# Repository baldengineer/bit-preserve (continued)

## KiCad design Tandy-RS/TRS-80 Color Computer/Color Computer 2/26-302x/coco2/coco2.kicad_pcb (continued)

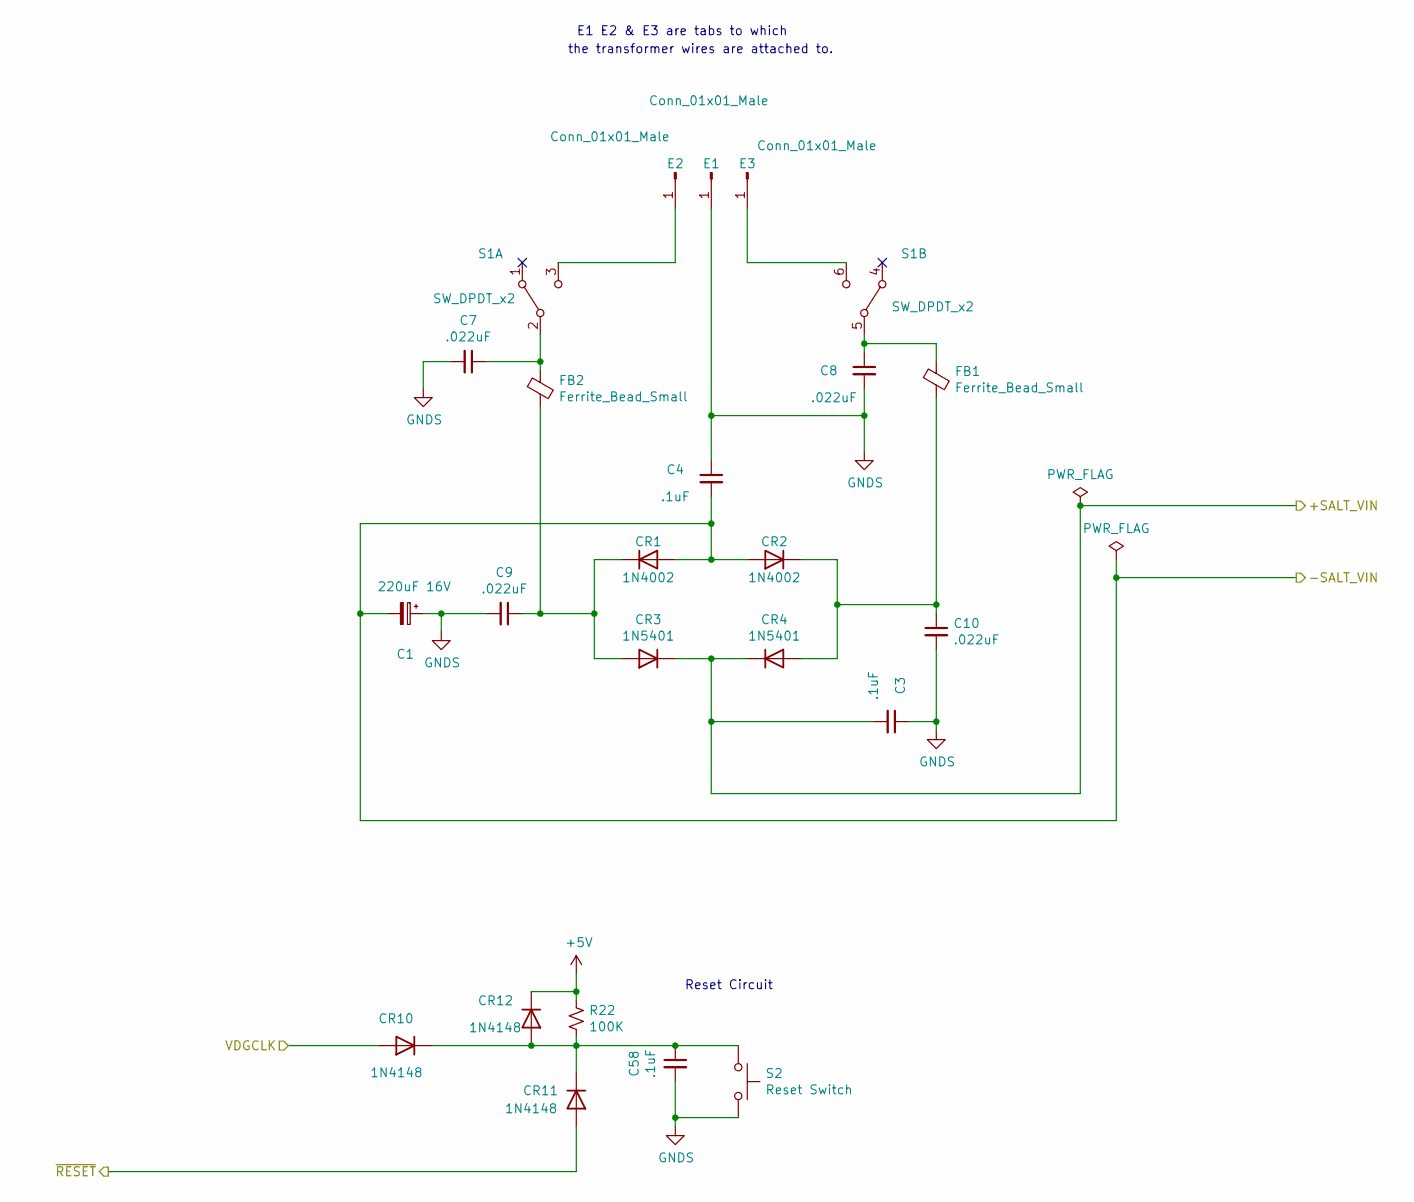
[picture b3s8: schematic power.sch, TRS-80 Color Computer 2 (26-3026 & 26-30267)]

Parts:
C1: 220uF 16V; CP_Radial_D8.0mm_P5.00mm; Manufacturer part# URS1C221MPD1TA
C3, C4, C58: .1uF; C_Axial_L3.8mm_D2.6mm_P10.00mm_Horizontal; Manufacturer part# A104K15X7RF5TAA
C7, C8, C9, C10: .022uF; C_Disc_D8.0mm_W2.5mm_P5.00mm; Manufacturer part# C317C223M5U5TA7301
CR1, CR2: 1N4002; D_DO-41_SOD81_P10.16mm_Horizontal; Manufacturer part# 1N4002G
CR3, CR4: 1N5401; D_DO-201AD_P15.24mm_Horizontal; Manufacturer part# 1N5401G-T
CR10, CR11, CR12: 1N4148; D_DO-35_SOD27_P7.62mm_Horizontal; Manufacturer part# 1N4148
E1, E2, E3: Conn_01x01_Male; Pin_D1.4mm_L8.5mm_W2.8mm_FlatFork; Manufacturer part# 1211
FB1, FB2: Ferrite_Bead_Small; ferrite_bead; Manufacturer part# 2743007111
R22: 100K; R_Axial_DIN0207_L6.3mm_D2.5mm_P10.16mm_Horizontal; Manufacturer part# CF14JT100K
S1: SW_DPDT_x2; F2UEE; Manufacturer part# F2UEE
S2: Reset Switch; B3F3152; Manufacturer part# B3F-3152

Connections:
+5V: CR12.1 (K), R22.1; also elsewhere on the board
/peripherals/+SALT_VIN: C3.2, CR3.1 (K), CR4.1 (K); also elsewhere on the board
/peripherals/-SALT_VIN: C1.2, C4.2, CR1.2 (A), CR2.2 (A); also elsewhere on the board
/power/VDGCLK: CR10.2 (A); also elsewhere on the board
/~RESET: CR11.2 (A); also elsewhere on the board
GNDS: C1.1, C3.1, C4.1, C7.2, C8.2, C9.2, C10.2, C58.2, E1.1, S2.2; also elsewhere on the board
unnamed: C7.1, FB2.1, S1.2 (B)
unnamed: C8.1, FB1.1, S1.5 (B)
unnamed: C9.1, CR1.1 (K), CR3.2 (A), FB2.2
unnamed: C10.1, CR2.1 (K), CR4.2 (A), FB1.2
unnamed: C58.1, CR10.1 (K), CR11.1 (K), CR12.2 (A), R22.2, S2.1
unnamed: E2.1, S1.3 (C)
unnamed: E3.1, S1.6 (C)

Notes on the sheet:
Reset Circuit
E1 E2 & E3 are tabs to which
the transformer wires are attached to.

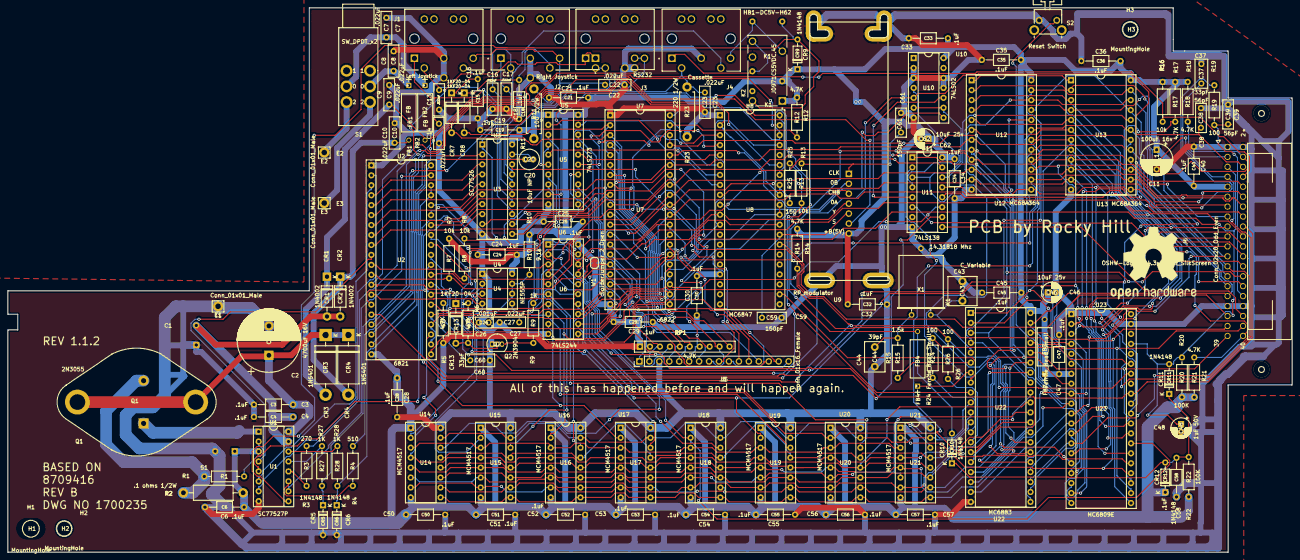
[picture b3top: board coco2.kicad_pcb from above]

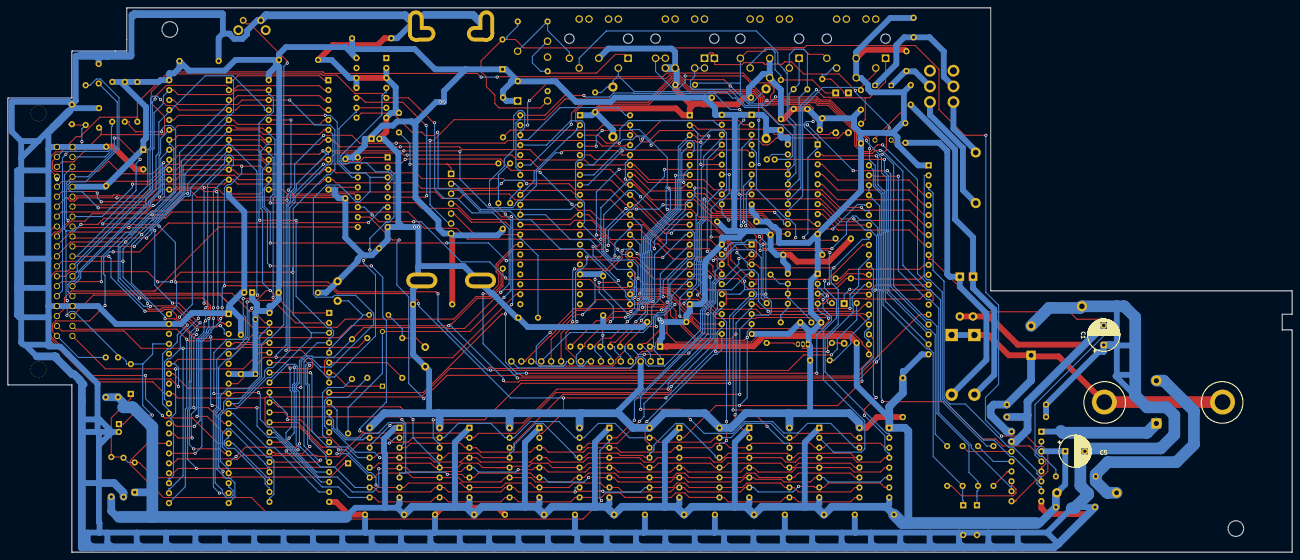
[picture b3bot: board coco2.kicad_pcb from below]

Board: 2 copper layers, 327.9 x 139.0 mm, 146 parts (2 on the bottom side), 169 nets.

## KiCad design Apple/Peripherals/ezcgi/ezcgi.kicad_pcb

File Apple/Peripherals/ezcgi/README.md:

This is a transcription into KiCad of Steve Ciarcia's E-Z Color Graphics
Interface, described in the [August 1982 issue of Byte magazine](https://archive.org/details/byte-magazine-1982-08).
It's not a line-for-line copy, but takes advantage of KiCad features that
wouldn't have been available 40 years ago.  

I originally posted this on
[GitLab](https://gitlab.com/salfter/a2-9918), and that's where you can also
find gerbers, a STEP model, and other extras, though KiCad 6 should be 
sufficient to regenerate those from the files presented here.  Parts are 
annotated with manufacturer and part-number fields, and current (as of 
December 2022) distributor SKUs are provided for all but the TMS9918A...
you'll need to trawl eBay for one of those.  

The sockets_*.kicad_sch sheets are present so that any BOM that you generate
will include sockets for all devices that can use them.

As with the schematic, the PCB layout isn't a 1:1 copy.  The article didn't
provide the author's original layout, so mine is what I came up with on my
own.  The components are laid out in a similar order, but the connections
between them are my own work.  I haven't yet had a chance to build this 
board.

KiCad has gotten better at including symbols and footprints in files, but
you might still find my [kicad-libs](https://gitlab.com/salfter/kicad-libs)
collection useful, especially if you want to modify these files or grab
symbols out of it (footprints are all stock KiCad, IIRC).

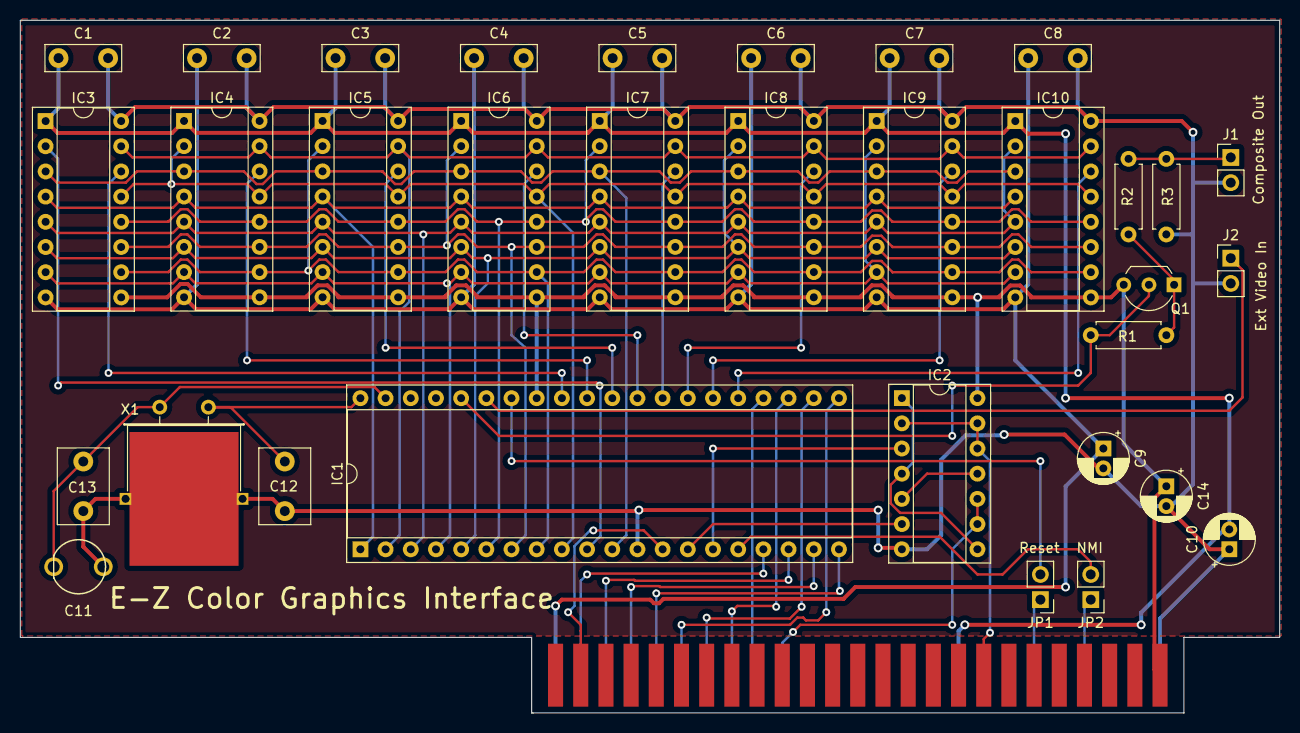
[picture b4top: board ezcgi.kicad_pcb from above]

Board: 2 copper layers, 127.0 x 69.9 mm, 34 parts (0 on the bottom side), 48 nets.

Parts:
C1, C2, C3, C4, C5, C6, C7, C8: 0.1µF; C_Disc_D7.5mm_W2.5mm_P5.00mm
C9, C10, C14: 10µF; CP_Radial_D5.0mm_P2.00mm
C11: 5-50pF; C_Trimmer_THT_5mm
C12, C13: 33pF; C_Disc_D7.5mm_W5.0mm_P5.00mm
IC1: TMS9918A; DIP-40_W15.24mm_Socket
IC2: 74LS00; DIP-14_W7.62mm_Socket
IC3, IC4, IC5, IC6, IC7, IC8, IC9, IC10: 4116; DIP-16_W7.62mm_Socket
J1: Composite Out; PinHeader_1x02_P2.54mm_Vertical
J2: Ext Video In (DNP); PinHeader_1x02_P2.54mm_Vertical
JP1, JP2: Jumper_2_Open; PinHeader_1x02_P2.54mm_Vertical
P1: A2Bus; Male_Card-Edge_50_pin__100_mil
Q1: 2N3904; TO-92_Inline_Wide
R1: 10kΩ; R_Axial_DIN0207_L6.3mm_D2.5mm_P7.62mm_Horizontal
R2, R3: 33Ω; R_Axial_DIN0207_L6.3mm_D2.5mm_P7.62mm_Horizontal
X1: 10.7386MHz; Crystal_HC49-U_Horizontal_1EP_style2

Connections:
+5V: C14.1, IC1.33 (VCC), IC2.14 (VCC), IC3.9 (VCC), IC4.9 (VCC), IC5.9 (VCC), IC6.9 (VCC), IC7.9 (VCC), IC8.9 (VCC), IC9.9 (VCC), IC10.9 (VCC), P1.25 (+5V), Q1.3 (C)
+12V: C2.1, C4.1, C6.1, C8.1, C9.1, IC3.8 (+12V), IC4.8 (+12V), IC5.8 (+12V), IC6.8 (+12V), IC7.8 (+12V), IC8.8 (+12V), IC9.8 (+12V), IC10.8 (+12V), P1.50 (+12V)
-5V: C1.2, C3.2, C5.2, C7.2, C10.2, IC3.1 (-5V), IC4.1 (-5V), IC5.1 (-5V), IC6.1 (-5V), IC7.1 (-5V), IC8.1 (-5V), IC9.1 (-5V), IC10.1 (-5V), P1.34 (-5V)
/RAM/A0: IC1.3 (AD7), IC3.5 (A0), IC4.5 (A0), IC5.5 (A0), IC6.5 (A0), IC7.5 (A0), IC8.5 (A0), IC9.5 (A0), IC10.2 (DIN), IC10.5 (A0)
/RAM/A1: IC1.4 (AD6), IC3.7 (A1), IC4.7 (A1), IC5.7 (A1), IC6.7 (A1), IC7.7 (A1), IC8.7 (A1), IC9.2 (DIN), IC9.7 (A1), IC10.7 (A1)
/RAM/A2: IC1.5 (AD5), IC3.6 (A2), IC4.6 (A2), IC5.6 (A2), IC6.6 (A2), IC7.6 (A2), IC8.2 (DIN), IC8.6 (A2), IC9.6 (A2), IC10.6 (A2)
/RAM/A3: IC1.6 (AD4), IC3.12 (A3), IC4.12 (A3), IC5.12 (A3), IC6.12 (A3), IC7.2 (DIN), IC7.12 (A3), IC8.12 (A3), IC9.12 (A3), IC10.12 (A3)
/RAM/A4: IC1.7 (AD3), IC3.11 (A4), IC4.11 (A4), IC5.11 (A4), IC6.2 (DIN), IC6.11 (A4), IC7.11 (A4), IC8.11 (A4), IC9.11 (A4), IC10.11 (A4)
/RAM/A5: IC1.8 (AD2), IC3.10 (A5), IC4.10 (A5), IC5.2 (DIN), IC5.10 (A5), IC6.10 (A5), IC7.10 (A5), IC8.10 (A5), IC9.10 (A5), IC10.10 (A5)
/RAM/A6: IC1.9 (AD1), IC3.13 (A6), IC4.2 (DIN), IC4.13 (A6), IC5.13 (A6), IC6.13 (A6), IC7.13 (A6), IC8.13 (A6), IC9.13 (A6), IC10.13 (A6)
/RAM/A7: IC1.10 (AD0), IC3.2 (DIN)
/RAM/D0: IC1.25 (RD7), IC10.14 (DOUT)
/RAM/D1: IC1.26 (RD6), IC9.14 (DOUT)
/RAM/D2: IC1.27 (RD5), IC8.14 (DOUT)
/RAM/D3: IC1.28 (RD4), IC7.14 (DOUT)
/RAM/D4: IC1.29 (RD3), IC6.14 (DOUT)
/RAM/D5: IC1.30 (RD2), IC5.14 (DOUT)
/RAM/D6: IC1.31 (RD1), IC4.14 (DOUT)
/RAM/D7: IC1.32 (RD0), IC3.14 (DOUT)
/RAM/R/~W: IC1.11 (R/~W), IC3.3 (~W), IC4.3 (~W), IC5.3 (~W), IC6.3 (~W), IC7.3 (~W), IC8.3 (~W), IC9.3 (~W), IC10.3 (~W)
/RAM/~CAS: IC1.2 (~CAS), IC3.15 (~CAS), IC4.15 (~CAS), IC5.15 (~CAS), IC6.15 (~CAS), IC7.15 (~CAS), IC8.15 (~CAS), IC9.15 (~CAS), IC10.15 (~CAS)
/RAM/~RAS: IC1.1 (~RAS), IC3.4 (~RAS), IC4.4 (~RAS), IC5.4 (~RAS), IC6.4 (~RAS), IC7.4 (~RAS), IC8.4 (~RAS), IC9.4 (~RAS), IC10.4 (~RAS)
A0: IC1.13 (MODE), P1.2 (A0)
D0: IC1.17 (D7), P1.49 (D0)
D1: IC1.18 (D6), P1.48 (D1)
D2: IC1.19 (D5), P1.47 (D2)
D3: IC1.20 (D4), P1.46 (D3)
D4: IC1.21 (D3), P1.45 (D4)
D5: IC1.22 (D2), P1.44 (D5)
D6: IC1.23 (D1), P1.43 (D6)
D7: IC1.24 (D0), P1.42 (D7)
GND: C1.1, C2.2, C3.1, C4.2, C5.1, C6.2, C7.1, C8.2, C9.2, C10.1, C11.1, C12.1, C13.1, C14.2, IC1.12 (GND), IC2.7 (GND), IC3.16 (GND), IC4.16 (GND), IC5.16 (GND), IC6.16 (GND), IC7.16 (GND), IC8.16 (GND), IC9.16 (GND), IC10.16 (GND), J1.2, J2.2, P1.26 (GND), R3.1, X1.3
unnamed: C11.2, C13.2, IC1.39 (XTAL2), X1.1
unnamed: C12.2, IC1.40 (XTAL1), X1.2
unnamed: IC1.14 (~CSW), IC2.6
unnamed: IC1.15 (~CSR), IC2.3
unnamed: IC1.16 (~INT), JP2.2 (B)
unnamed: IC1.34 (~RESET/SYNC), JP1.2 (B)
unnamed: IC1.35 (EXTV), J2.1
unnamed: IC1.36 (COMVID), Q1.2 (B), R1.2
unnamed: IC2.1, IC2.4, IC2.8
unnamed: IC2.5, IC2.11
unnamed: J1.1, R2.1, R3.2
unnamed: Q1.1 (E), R1.1, R2.2
R/~W: IC2.2, IC2.12, IC2.13, P1.18 (R/~W)
~DEVSEL: IC2.9, IC2.10, P1.41 (~DEVSEL)
~NMI: JP2.1 (A), P1.29 (~NMI)
~RES: JP1.1 (A), P1.31 (~RES)

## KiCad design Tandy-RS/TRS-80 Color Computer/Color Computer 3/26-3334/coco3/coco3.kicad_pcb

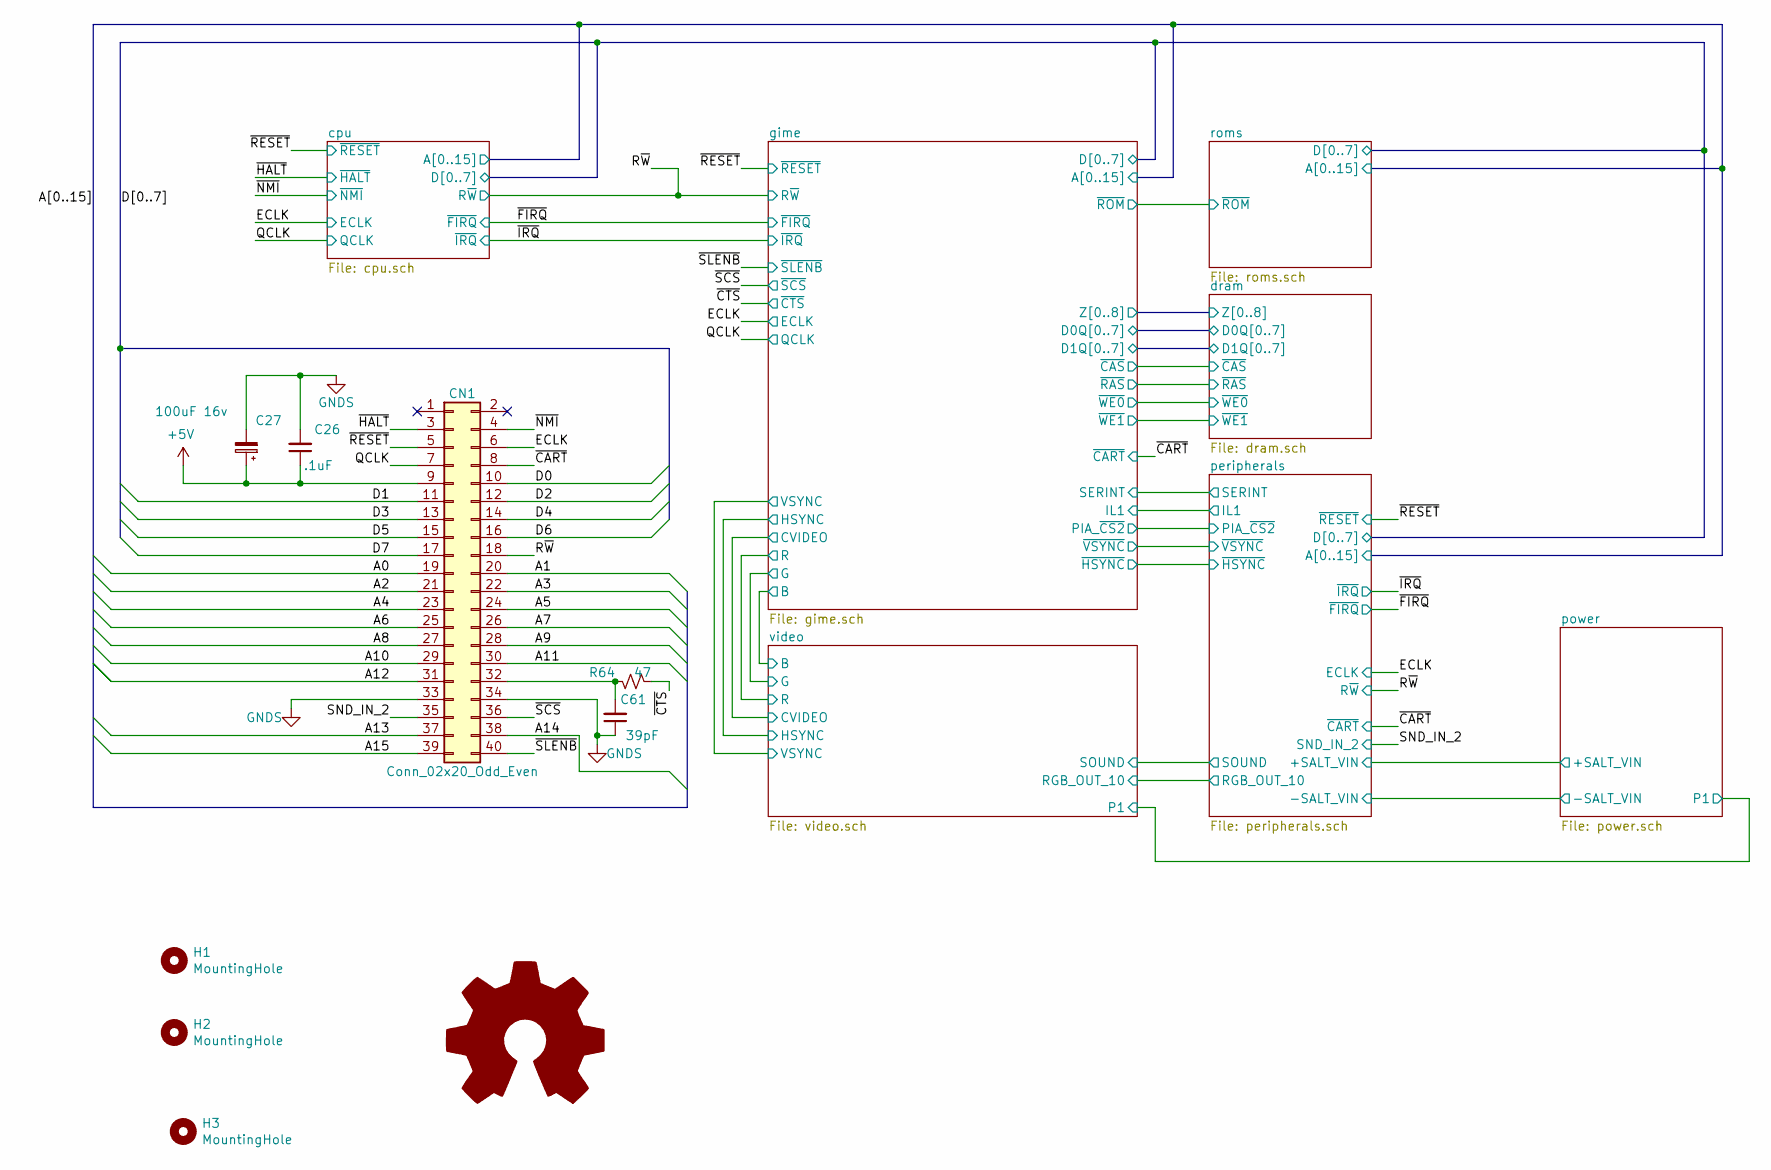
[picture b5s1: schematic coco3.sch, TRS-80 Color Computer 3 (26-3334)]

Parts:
C26: .1uF; C_Disc_D4.7mm_W2.5mm_P5.00mm; Manufacturer part# FG28C0G1H103JNT06
C27: 100uF 16v; CP_Radial_D8.0mm_P5.00mm; Manufacturer part# UST1C101MDD1TA
C61: 39pF; C_Disc_D4.7mm_W2.5mm_P5.00mm; Manufacturer part# K390J15C0GF5TL2
CN1: Conn_02x20_Odd_Even; EBC20DRAS; Manufacturer part# EBC20DRAS
H1, H2: MountingHole; MountingHole_3.5mm
H3: MountingHole; coco3_outline_and_layout
R64: 47; R_Axial_DIN0207_L6.3mm_D2.5mm_P10.16mm_Horizontal; Manufacturer part# CF14JT47R0

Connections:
+5V: C26.1, C27.1, CN1.9; also elsewhere on the board
/A0: CN1.19; also elsewhere on the board
/A1: CN1.20; also elsewhere on the board
/A2: CN1.21; also elsewhere on the board
/A3: CN1.22; also elsewhere on the board
/A4: CN1.23; also elsewhere on the board
/A5: CN1.24; also elsewhere on the board
/A6: CN1.25; also elsewhere on the board
/A7: CN1.26; also elsewhere on the board
/A8: CN1.27; also elsewhere on the board
/A9: CN1.28; also elsewhere on the board
/A10: CN1.29; also elsewhere on the board
/A11: CN1.30; also elsewhere on the board
/A12: CN1.31; also elsewhere on the board
/A13: CN1.37; also elsewhere on the board
/A14: CN1.38; also elsewhere on the board
/A15: CN1.39; also elsewhere on the board
/D0: CN1.10; also elsewhere on the board
/D1: CN1.11; also elsewhere on the board
/D2: CN1.12; also elsewhere on the board
/D3: CN1.13; also elsewhere on the board
/D4: CN1.14; also elsewhere on the board
/D5: CN1.15; also elsewhere on the board
/D6: CN1.16; also elsewhere on the board
/D7: CN1.17; also elsewhere on the board
/ECLK: CN1.6; also elsewhere on the board
/QCLK: CN1.7; also elsewhere on the board
/R~W: CN1.18; also elsewhere on the board
/SND_IN_2: CN1.35; also elsewhere on the board
/~CART: CN1.8; also elsewhere on the board
/~CTS: R64.1; also elsewhere on the board
/~HALT: CN1.3; also elsewhere on the board
/~NMI: CN1.4; also elsewhere on the board
/~RESET: CN1.5; also elsewhere on the board
/~SCS: CN1.36; also elsewhere on the board
/~SLENB: CN1.40; also elsewhere on the board
GNDS: C26.2, C27.2, C61.1, CN1.33, CN1.34; also elsewhere on the board
unnamed: C61.2, CN1.32, R64.2

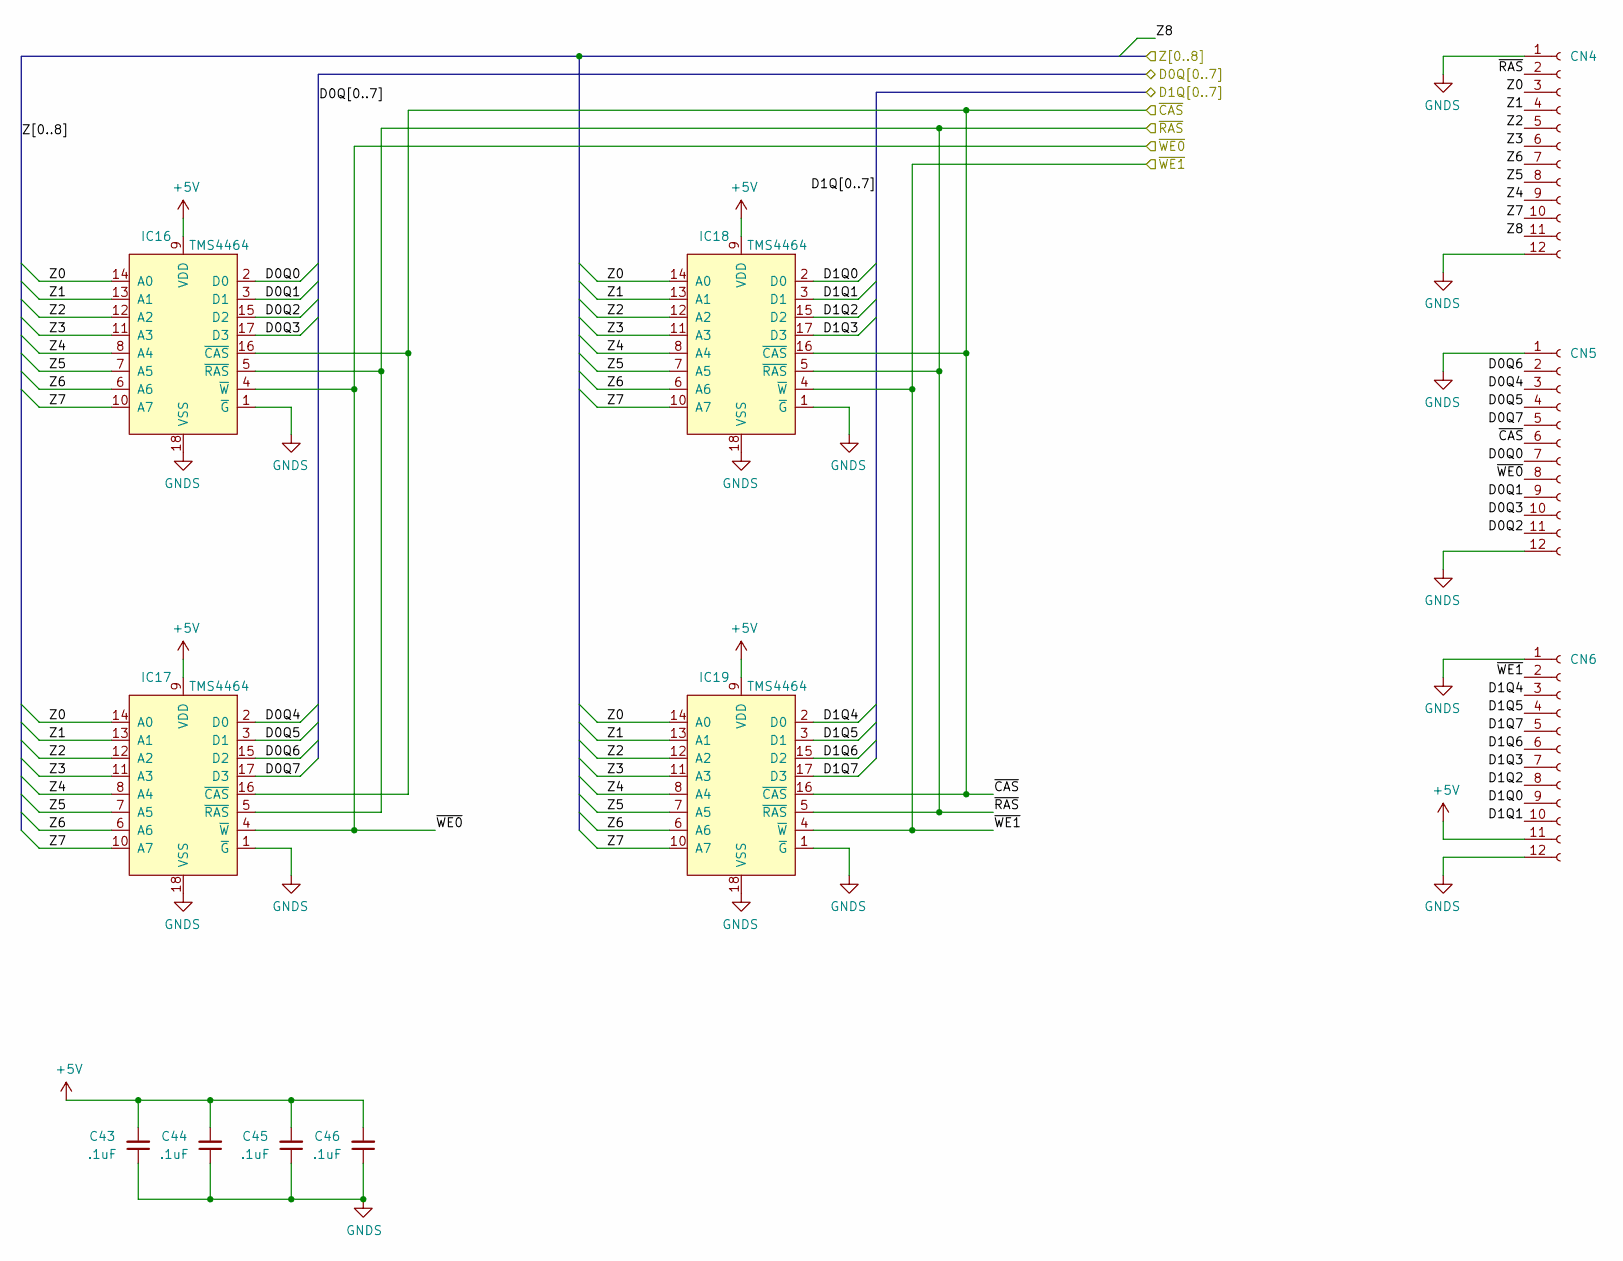
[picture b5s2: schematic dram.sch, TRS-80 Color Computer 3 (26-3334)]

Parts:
C43, C44, C45, C46: .1uF; C_Disc_D4.7mm_W2.5mm_P5.00mm; Manufacturer part# FG28C0G1H103JNT06
CN4, CN5, CN6: Conn_01x12_Female; PinSocket_1x12_P2.54mm_for_memory_board_adapter; Manufacturer part# 0022182121
IC16, IC17, IC18, IC19: TMS4464; DIP-18_W7.62mm_Socket; Manufacturer part# A 18-LC-TT

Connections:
+5V: C43.2, C44.2, C45.2, C46.2, CN6.11, IC16.9 (VDD), IC17.9 (VDD), IC18.9 (VDD), IC19.9 (VDD); also elsewhere on the board
/dram/D0Q0: CN5.7, IC16.2 (D0); also elsewhere on the board
/dram/D0Q1: CN5.9, IC16.3 (D1); also elsewhere on the board
/dram/D0Q2: CN5.11, IC16.15 (D2); also elsewhere on the board
/dram/D0Q3: CN5.10, IC16.17 (D3); also elsewhere on the board
/dram/D0Q4: CN5.3, IC17.2 (D0); also elsewhere on the board
/dram/D0Q5: CN5.4, IC17.3 (D1); also elsewhere on the board
/dram/D0Q6: CN5.2, IC17.15 (D2); also elsewhere on the board
/dram/D0Q7: CN5.5, IC17.17 (D3); also elsewhere on the board
/dram/D1Q0: CN6.9, IC18.2 (D0); also elsewhere on the board
/dram/D1Q1: CN6.10, IC18.3 (D1); also elsewhere on the board
/dram/D1Q2: CN6.8, IC18.15 (D2); also elsewhere on the board
/dram/D1Q3: CN6.7, IC18.17 (D3); also elsewhere on the board
/dram/D1Q4: CN6.3, IC19.2 (D0); also elsewhere on the board
/dram/D1Q5: CN6.4, IC19.3 (D1); also elsewhere on the board
/dram/D1Q6: CN6.6, IC19.15 (D2); also elsewhere on the board
/dram/D1Q7: CN6.5, IC19.17 (D3); also elsewhere on the board
/dram/Z0: CN4.3, IC16.14 (A0), IC17.14 (A0), IC18.14 (A0), IC19.14 (A0); also elsewhere on the board
/dram/Z1: CN4.4, IC16.13 (A1), IC17.13 (A1), IC18.13 (A1), IC19.13 (A1); also elsewhere on the board
/dram/Z2: CN4.5, IC16.12 (A2), IC17.12 (A2), IC18.12 (A2), IC19.12 (A2); also elsewhere on the board
/dram/Z3: CN4.6, IC16.11 (A3), IC17.11 (A3), IC18.11 (A3), IC19.11 (A3); also elsewhere on the board
/dram/Z4: CN4.9, IC16.8 (A4), IC17.8 (A4), IC18.8 (A4), IC19.8 (A4); also elsewhere on the board
/dram/Z5: CN4.8, IC16.7 (A5), IC17.7 (A5), IC18.7 (A5), IC19.7 (A5); also elsewhere on the board
/dram/Z6: CN4.7, IC16.6 (A6), IC17.6 (A6), IC18.6 (A6), IC19.6 (A6); also elsewhere on the board
/dram/Z7: CN4.10, IC16.10 (A7), IC17.10 (A7), IC18.10 (A7), IC19.10 (A7); also elsewhere on the board
/dram/Z8: CN4.11; also elsewhere on the board
/dram/~CAS: CN5.6, IC16.16 (~CAS), IC17.16 (~CAS), IC18.16 (~CAS), IC19.16 (~CAS); also elsewhere on the board
/dram/~RAS: CN4.2, IC16.5 (~RAS), IC17.5 (~RAS), IC18.5 (~RAS), IC19.5 (~RAS); also elsewhere on the board
/dram/~WE0: CN5.8, IC16.4 (~W), IC17.4 (~W); also elsewhere on the board
/dram/~WE1: CN6.2, IC18.4 (~W), IC19.4 (~W); also elsewhere on the board
GNDS: C43.1, C44.1, C45.1, C46.1, CN4.1, CN4.12, CN5.1, CN5.12, CN6.1, CN6.12, IC16.1 (~G), IC16.18 (VSS), IC17.1 (~G), IC17.18 (VSS), IC18.1 (~G), IC18.18 (VSS), IC19.1 (~G), IC19.18 (VSS); also elsewhere on the board

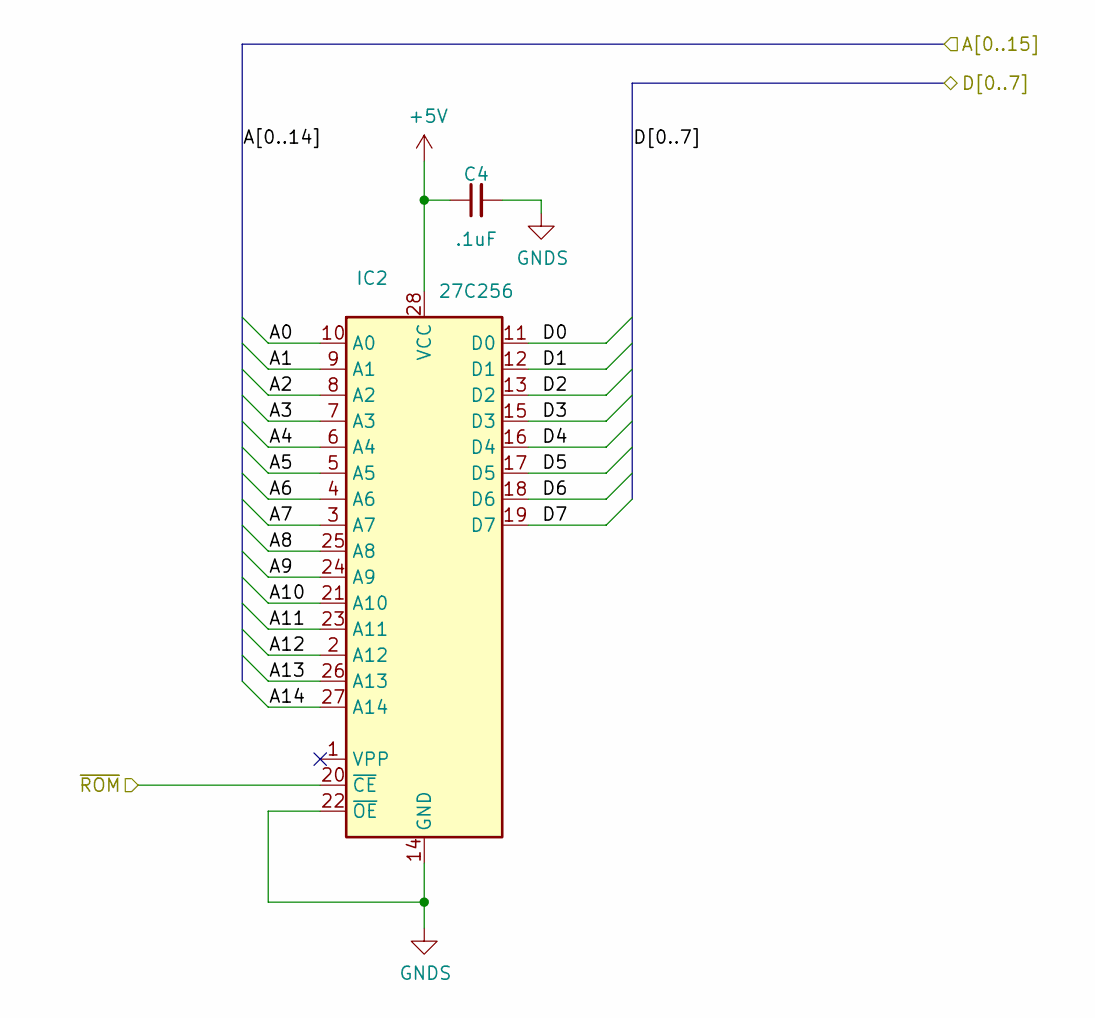
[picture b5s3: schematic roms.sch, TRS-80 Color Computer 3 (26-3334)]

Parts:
C4: .1uF; C_Disc_D4.7mm_W2.5mm_P5.00mm; Manufacturer part# FG28C0G1H103JNT06
IC2: 27C256; DIP-28_W15.24mm_Socket; Manufacturer part# AT27C256R-45PU

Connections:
+5V: C4.1, IC2.28 (VCC); also elsewhere on the board
/A0: IC2.10 (A0); also elsewhere on the board
/A1: IC2.9 (A1); also elsewhere on the board
/A2: IC2.8 (A2); also elsewhere on the board
/A3: IC2.7 (A3); also elsewhere on the board
/A4: IC2.6 (A4); also elsewhere on the board
/A5: IC2.5 (A5); also elsewhere on the board
/A6: IC2.4 (A6); also elsewhere on the board
/A7: IC2.3 (A7); also elsewhere on the board
/A8: IC2.25 (A8); also elsewhere on the board
/A9: IC2.24 (A9); also elsewhere on the board
/A10: IC2.21 (A10); also elsewhere on the board
/A11: IC2.23 (A11); also elsewhere on the board
/A12: IC2.2 (A12); also elsewhere on the board
/A13: IC2.26 (A13); also elsewhere on the board
/A14: IC2.27 (A14); also elsewhere on the board
/D0: IC2.11 (D0); also elsewhere on the board
/D1: IC2.12 (D1); also elsewhere on the board
/D2: IC2.13 (D2); also elsewhere on the board
/D3: IC2.15 (D3); also elsewhere on the board
/D4: IC2.16 (D4); also elsewhere on the board
/D5: IC2.17 (D5); also elsewhere on the board
/D6: IC2.18 (D6); also elsewhere on the board
/D7: IC2.19 (D7); also elsewhere on the board
/gime/~ROM: IC2.20 (~CE); also elsewhere on the board
GNDS: C4.2, IC2.14 (GND), IC2.22 (~OE); also elsewhere on the board

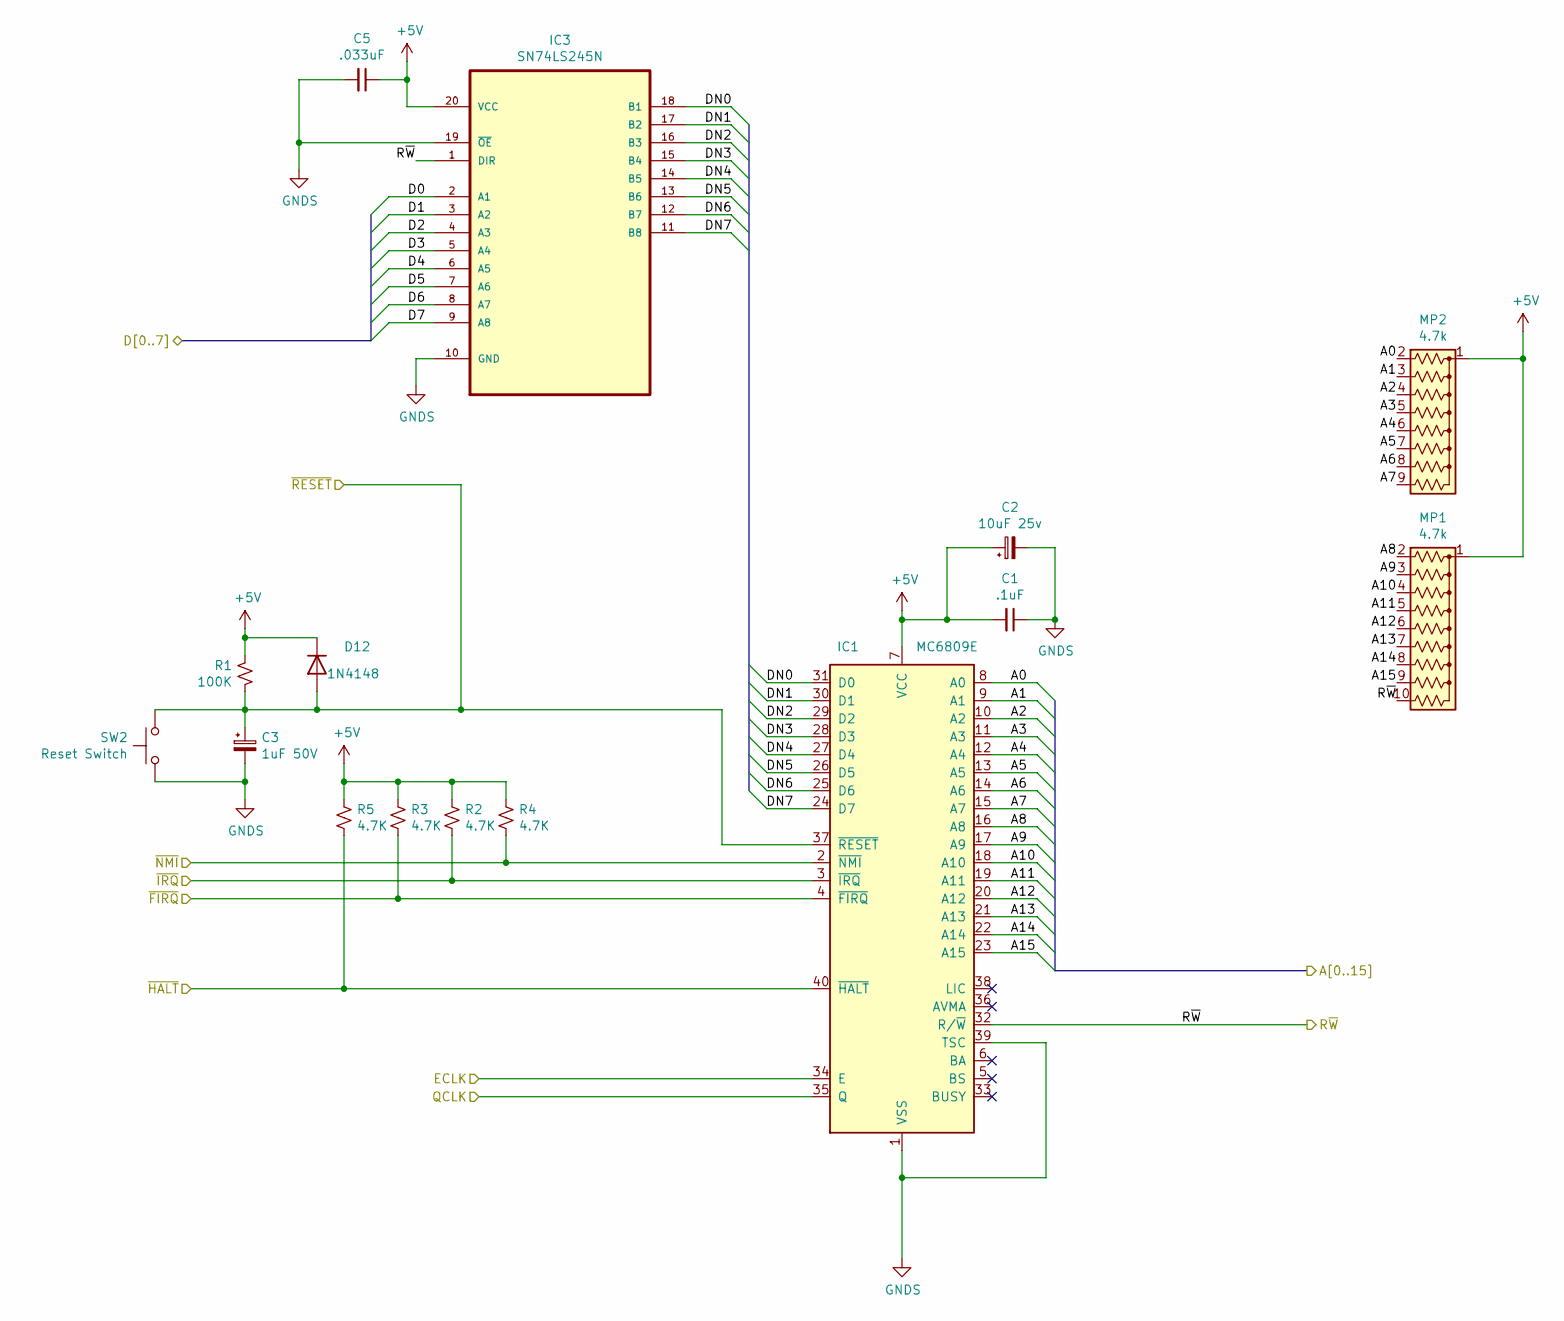
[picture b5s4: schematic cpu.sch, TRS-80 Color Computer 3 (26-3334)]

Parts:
C1: .1uF; C_Disc_D4.7mm_W2.5mm_P5.00mm; Manufacturer part# FG28C0G1H103JNT06
C2: 10uF 25v; CP_Radial_D5.0mm_P2.00mm; Manufacturer part# UPW1E100MDD
C3: 1uF 50V; CP_Radial_D5.0mm_P2.00mm; Manufacturer part# 515D105M050JA6AE3
C5: .033uF; C_Axial_L5.1mm_D3.1mm_P10.00mm_Horizontal; Manufacturer part# C410C333K5R5TA7200
D12: 1N4148; D_DO-35_SOD27_P7.62mm_Horizontal; Manufacturer part# 1N4148
IC1: MC6809E; DIP-40_W15.24mm_Socket; Manufacturer part# ED40DT
IC3: SN74LS245N; DIP-20_W7.62mm_Socket; Manufacturer part# SN74LS245N
MP1: 4.7k; R_Array_SIP10; Manufacturer part# 770101472P
MP2: 4.7k; R_Array_SIP9; Manufacturer part# 4609H-101-472LF
R1: 100K; R_Axial_DIN0207_L6.3mm_D2.5mm_P10.16mm_Horizontal; Manufacturer part# MFR-25FBF52-100K
R2, R3, R4, R5: 4.7K; R_Axial_DIN0207_L6.3mm_D2.5mm_P10.16mm_Horizontal; Manufacturer part# Stackpole Electronics Inc
SW2: Reset Switch; B3F3152; Manufacturer part# B3F-3152

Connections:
+5V: C1.2, C2.1, C5.1, D12.1 (K), IC1.7 (VCC), IC3.20 (VCC), MP1.1 (common), MP2.1 (common), R1.1, R2.1, R3.1, R4.1, R5.1; also elsewhere on the board
/A0: IC1.8 (A0), MP2.2 (R1); also elsewhere on the board
/A1: IC1.9 (A1), MP2.3 (R2); also elsewhere on the board
/A2: IC1.10 (A2), MP2.4 (R3); also elsewhere on the board
/A3: IC1.11 (A3), MP2.5 (R4); also elsewhere on the board
/A4: IC1.12 (A4), MP2.6 (R5); also elsewhere on the board
/A5: IC1.13 (A5), MP2.7 (R6); also elsewhere on the board
/A6: IC1.14 (A6), MP2.8 (R7); also elsewhere on the board
/A7: IC1.15 (A7), MP2.9 (R8); also elsewhere on the board
/A8: IC1.16 (A8), MP1.2 (R1); also elsewhere on the board
/A9: IC1.17 (A9), MP1.3 (R2); also elsewhere on the board
/A10: IC1.18 (A10), MP1.4 (R3); also elsewhere on the board
/A11: IC1.19 (A11), MP1.5 (R4); also elsewhere on the board
/A12: IC1.20 (A12), MP1.6 (R5); also elsewhere on the board
/A13: IC1.21 (A13), MP1.7 (R6); also elsewhere on the board
/A14: IC1.22 (A14), MP1.8 (R7); also elsewhere on the board
/A15: IC1.23 (A15), MP1.9 (R8); also elsewhere on the board
/D0: IC3.2 (A1); also elsewhere on the board
/D1: IC3.3 (A2); also elsewhere on the board
/D2: IC3.4 (A3); also elsewhere on the board
/D3: IC3.5 (A4); also elsewhere on the board
/D4: IC3.6 (A5); also elsewhere on the board
/D5: IC3.7 (A6); also elsewhere on the board
/D6: IC3.8 (A7); also elsewhere on the board
/D7: IC3.9 (A8); also elsewhere on the board
/ECLK: IC1.34 (E); also elsewhere on the board
/QCLK: IC1.35 (Q); also elsewhere on the board
/R~W: IC1.32 (R/~W), IC3.1 (DIR), MP1.10 (R9); also elsewhere on the board
/cpu/DN0: IC1.31 (D0), IC3.18 (B1)
/cpu/DN1: IC1.30 (D1), IC3.17 (B2)
/cpu/DN2: IC1.29 (D2), IC3.16 (B3)
/cpu/DN3: IC1.28 (D3), IC3.15 (B4)
/cpu/DN4: IC1.27 (D4), IC3.14 (B5)
/cpu/DN5: IC1.26 (D5), IC3.13 (B6)
/cpu/DN6: IC1.25 (D6), IC3.12 (B7)
/cpu/DN7: IC1.24 (D7), IC3.11 (B8)
/~FIRQ: IC1.4 (~FIRQ), R3.2; also elsewhere on the board
/~HALT: IC1.40 (~HALT), R5.2; also elsewhere on the board
/~IRQ: IC1.3 (~IRQ), R2.2; also elsewhere on the board
/~NMI: IC1.2 (~NMI), R4.2; also elsewhere on the board
/~RESET: C3.1, D12.2 (A), IC1.37 (~RESET), R1.2, SW2.1; also elsewhere on the board
GNDS: C1.1, C2.2, C3.2, C5.2, IC1.1 (VSS), IC1.39 (TSC), IC3.10 (GND), IC3.19 (~OE), SW2.2; also elsewhere on the board
